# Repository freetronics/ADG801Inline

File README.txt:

=ADG801 Inline

Power control module used in ArduSat-X and ArduSat-1 to cycle GPS
module power under software control, as a fix for lack of power
control on the GPS header of the Payload Processor Module.

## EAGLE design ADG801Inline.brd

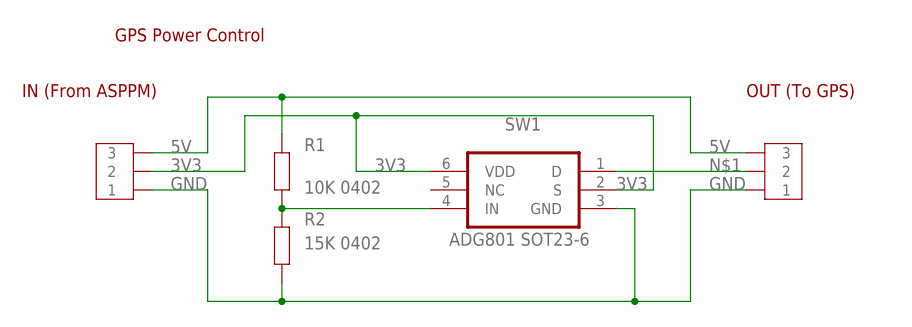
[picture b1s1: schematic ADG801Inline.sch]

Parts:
JP1, JP2: 3PIN_SMD; 1X3-2MM
R1: 10K 0402; 0402
R2: 15K 0402; 0402
SW1: ADG801 SOT23-6; SOT23-6

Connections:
3V3: JP1.P$2 (2), SW1.2 (S), SW1.6 (VDD)
5V: JP1.P$3 (3), JP2.P$3 (3), R1.2
GND: JP1.P$1 (1), JP2.P$1 (1), R2.1, SW1.3 (GND)
unnamed: JP2.P$2 (2), SW1.1 (D)
unnamed: R1.1, R2.2, SW1.4 (IN)

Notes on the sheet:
GPS Power Control
IN (From ASPPM)
OUT (To GPS)

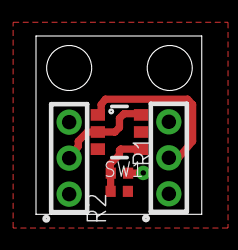
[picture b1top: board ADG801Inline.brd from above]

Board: 4 copper layers, 9.2 x 9.9 mm, 5 parts (0 on the bottom side), 5 nets.

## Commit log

2018-03-21 Initial import of very old project
